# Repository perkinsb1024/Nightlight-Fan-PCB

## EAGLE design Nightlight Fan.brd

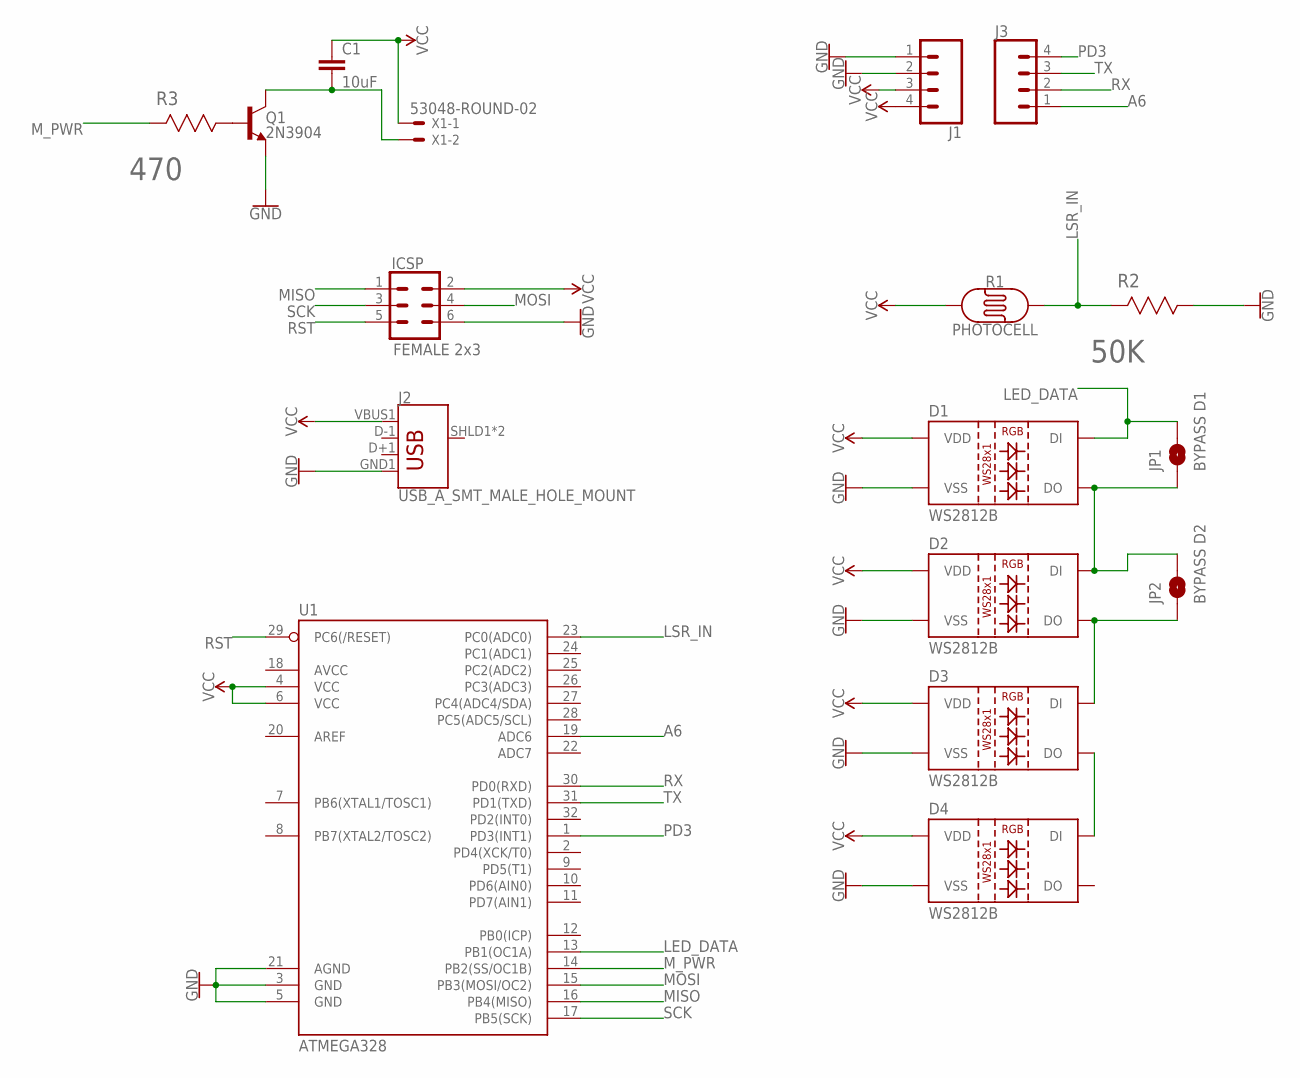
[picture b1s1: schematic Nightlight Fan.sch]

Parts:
C1: 10uF; 0805
D1, D2, D3, D4: WS2812B
ICSP: FEMALE 2x3; 2X3
J1, J3: CONN_041X04_NO_SILK; 1X04_NO_SILK
J2: USB_A_SMT_MALE_HOLE_MOUNT; USB_A_SMT_MALE
JP1: BYPASS D1; SMT-JUMPER_2_NO_SILK
JP2: BYPASS D2; SMT-JUMPER_2_NO_SILK
Q1: 2N3904; SOT23-3
R1: PHOTOCELL
R2: 50K; RESC2013X65N
R3: 470; RESC2013X65N
U1: ATMEGA328; TQFP32-08
X1: 53048-ROUND-02; 53048-02

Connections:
A6: J3.1, U1.19 (ADC6)
GND: D1.3 (VSS), D2.3 (VSS), D3.3 (VSS), D4.3 (VSS), ICSP.6, J1.1, J1.2, J2.GND1 (GND), Q1.2 (E), R2.1, U1.3 (GND), U1.5 (GND), U1.21 (AGND)
LED_DATA: D1.4 (DI), JP1.2, U1.13 (PB1(OC1A))
LSR_IN: R1.2, R2.2, U1.23 (PC0(ADC0))
MISO: ICSP.1, U1.16 (PB4(MISO))
MOSI: ICSP.4, U1.15 (PB3(MOSI/OC2))
M_PWR: R3.2, U1.14 (PB2(SS/OC1B))
unnamed: D1.2 (DO), D2.4 (DI), JP1.1, JP2.2
unnamed: D2.2 (DO), D3.4 (DI), JP2.1
unnamed: D3.2 (DO), D4.4 (DI)
unnamed: Q1.1 (B), R3.1
unnamed: C1.2, Q1.3 (C), X1.2
PD3: J3.4, U1.1 (PD3(INT1))
RST: ICSP.5, U1.29 (PC6(/RESET))
RX: J3.2, U1.30 (PD0(RXD))
SCK: ICSP.3, U1.17 (PB5(SCK))
TX: J3.3, U1.31 (PD1(TXD))
VCC: C1.1, D1.1 (VDD), D2.1 (VDD), D3.1 (VDD), D4.1 (VDD), ICSP.2, J1.3, J1.4, J2.VBUS1 (VBUS), R1.1, U1.4 (VCC), U1.6 (VCC), X1.1

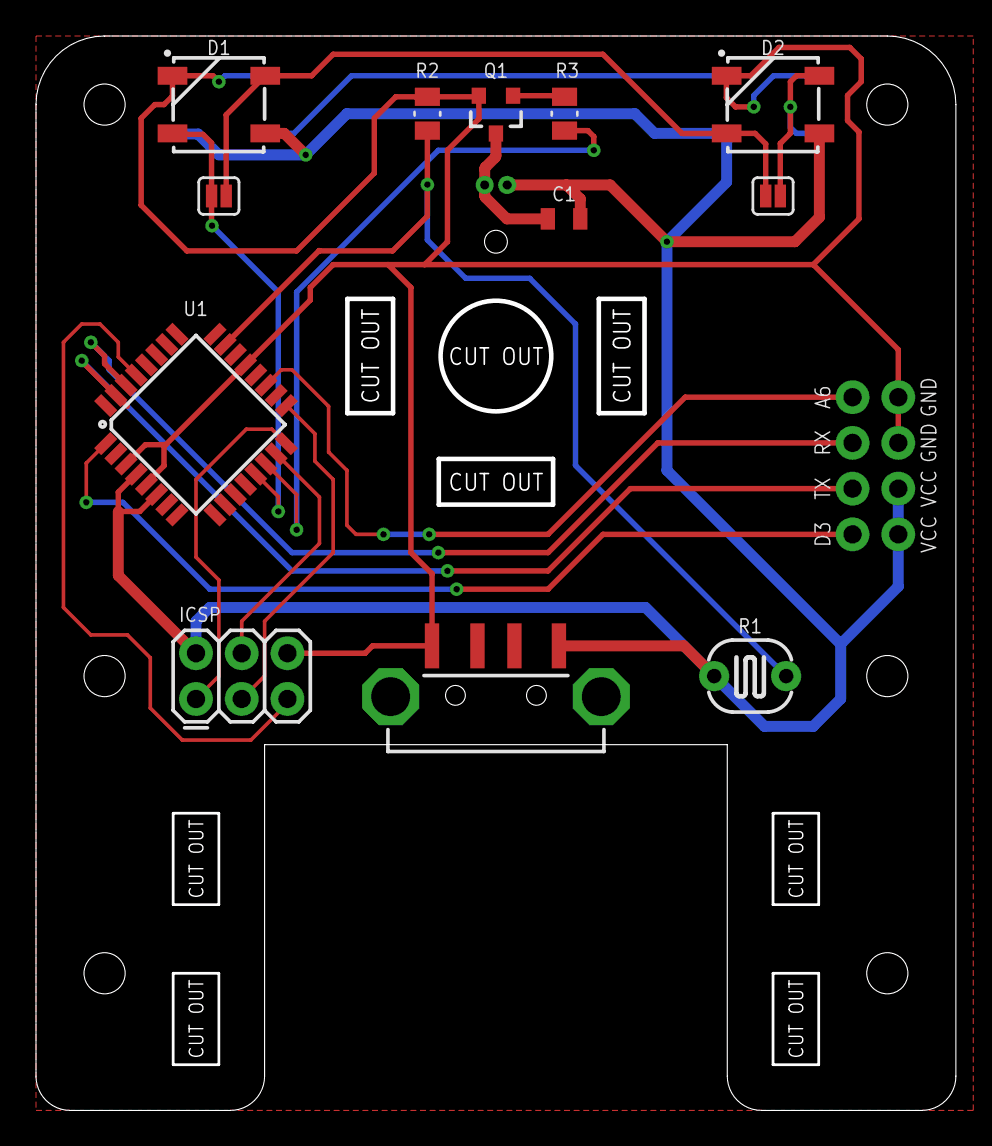
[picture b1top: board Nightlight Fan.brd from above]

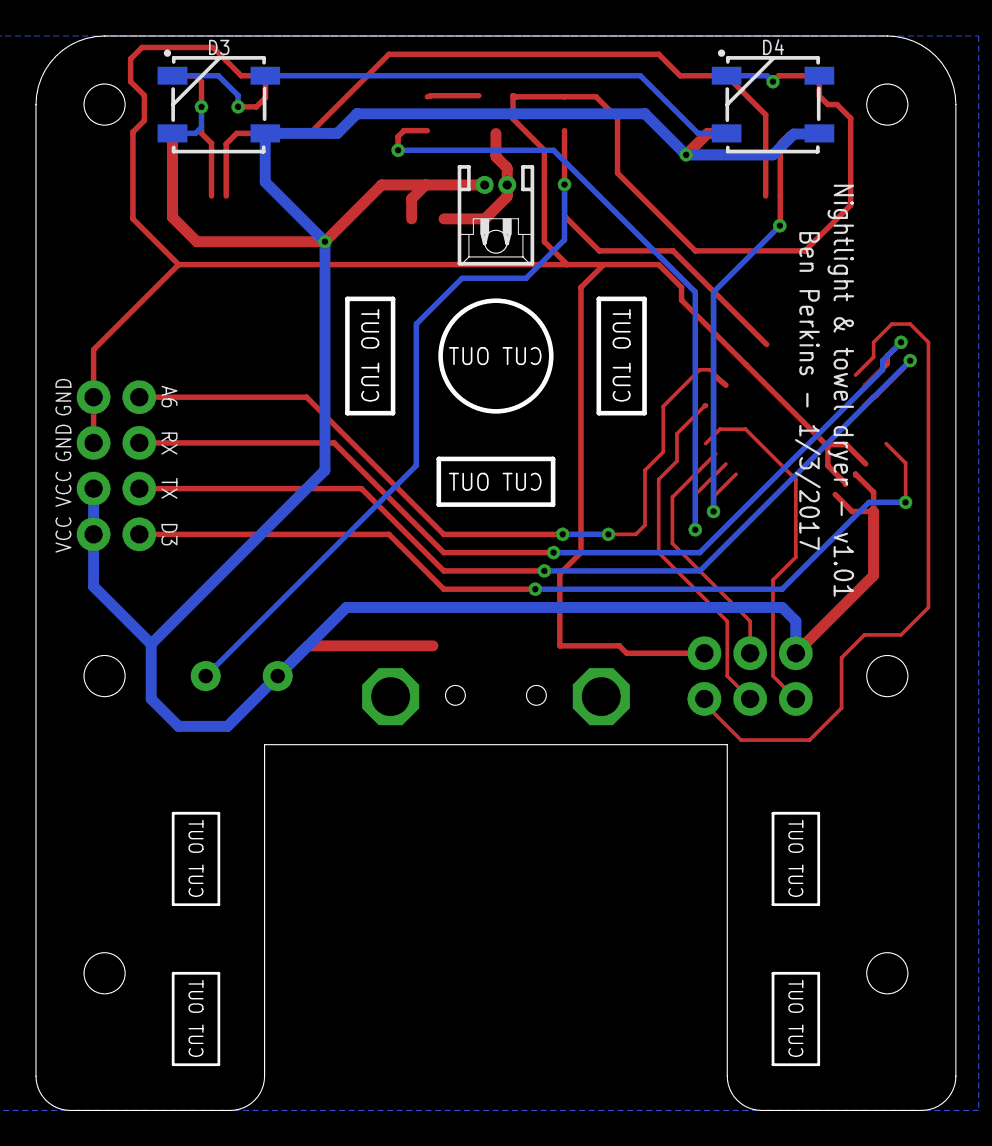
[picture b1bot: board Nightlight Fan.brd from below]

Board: 2 copper layers, 50.9 x 59.4 mm, 17 parts (3 on the bottom side), 18 nets.

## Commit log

2018-01-04 Nightlight Fan v1.0
2018-01-04 v1.01 - Moved USB port slightly beyond PCB edge, increased motor wire relief hole size

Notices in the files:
parts and their libraries:
SparkFun-Connectors: Licensing: Creative Commons ShareAlike 4.0 International - https://creativecommons.org/licenses/by-sa/4.0
